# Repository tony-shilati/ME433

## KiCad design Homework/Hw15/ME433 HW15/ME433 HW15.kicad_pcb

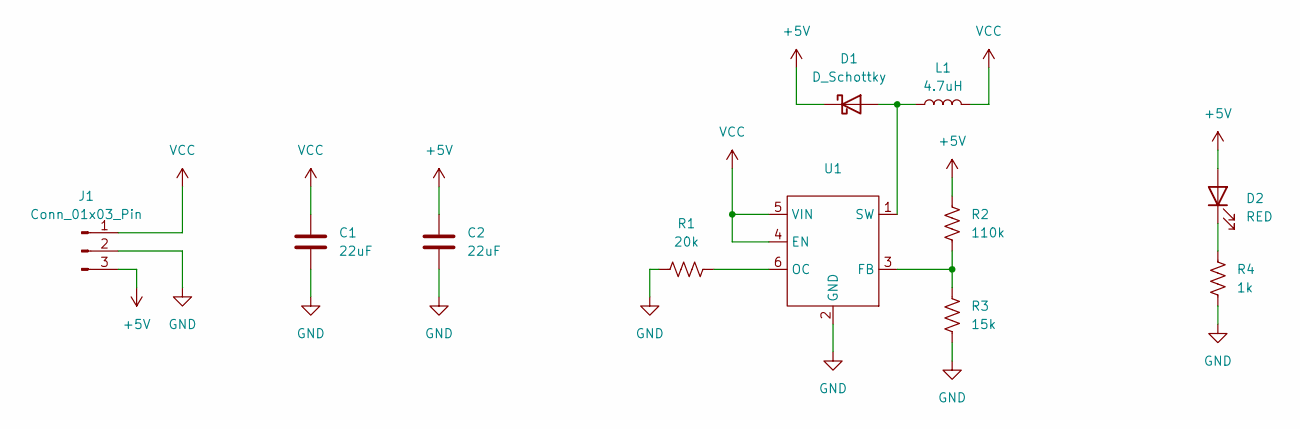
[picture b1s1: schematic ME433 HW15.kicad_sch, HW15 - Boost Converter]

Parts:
C1, C2: 22uF; C_0805_2012Metric
D1: D_Schottky; D_SOD-123
D2: RED; LED_0603_1608Metric
J1: Conn_01x03_Pin; PinHeader_1x03_P2.54mm_Vertical
L1: 4.7uH; L_0603_1608Metric
R1: 20k; R_0603_1608Metric
R2: 110k; R_0402_1005Metric
R3: 15k; R_0402_1005Metric
R4: 1k; R_0603_1608Metric
U1: TSOT-23-6_HandSoldering

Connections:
+5V: C2.1, D1.1 (K), D2.2 (A), J1.3, R2.1
GND: C1.2, C2.2, J1.2, R1.1, R3.2, R4.2, U1.2 (GND)
unnamed: D1.2 (A), L1.1, U1.1 (SW)
unnamed: D2.1 (K), R4.1
unnamed: R2.2, R3.1, U1.3 (FB)
unnamed: R1.2, U1.6 (OC)
VCC: C1.1, J1.1, L1.2, U1.4 (EN), U1.5 (VIN)

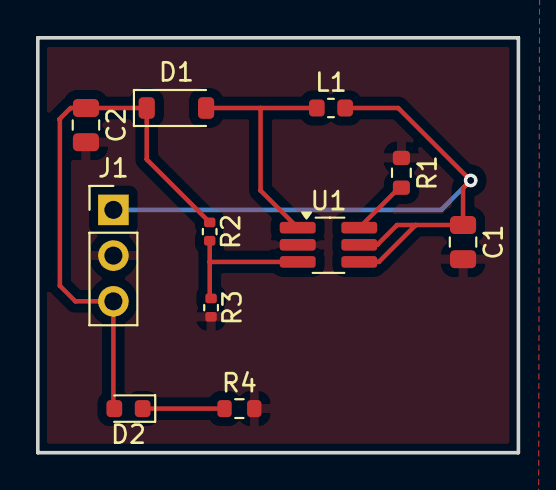
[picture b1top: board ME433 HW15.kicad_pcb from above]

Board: 2 copper layers, 26.7 x 23.0 mm, 11 parts (0 on the bottom side), 7 nets.

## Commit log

2025-04-08 Added hello_gpio_irq and hello_usb
2025-04-08 Removed .DS_Store
2025-04-08 Everything working in Homework 2
2025-04-09 Added the sample code from homework3 on github and ran it
2025-04-09 Most of homework 3 complete.
2025-04-09 Added a picture of the Pico pinout
2025-04-09 I think the Homework 3 code completely works. Still need to check it all
2025-04-12 renamed homework folders and added Hw4 pico project
2025-04-12 Added spi functionality and checked it on the nlab
2025-04-12 Seeing a saw wave on the nlab
2025-04-12 Saw wave is correct amplitude
2025-04-12 Generates a 2Hz triangle wave
2025-04-12 Generates a 1 Hz triangle wave
2025-04-12 Hw4 generates a 2Hz sin wave
2025-04-17 Added a hw5 folder and copied dome of the SPI code from hw4
2025-04-17 Added Waves image for hw4
2025-04-17 Added more spi code
2025-04-18 Wrote a foor loop in the initiation phse, which writes the waveform to the RAM
2025-04-19 Progress. Writing something to the RAM
2025-04-19 Its working git add --all
2025-04-19 added a photo of the waveform and the math
2025-04-21 Added a hearbeat LED
2025-04-21 Pico turns on the LED on startup using the external gpio
2025-04-21 Button and LED work on the external gpio
2025-04-21 Switched the heartbeat LED to be the builtin green led
2025-04-21 Added the vide and rope link
2025-04-23 Added a 1Hz hearbeat LED and downloaded sample code for display
2025-04-23 Made a fun program that sweeps a line back and forth across the display
2025-04-24 Added the font header file
2025-04-24 LED displays each ASCII character on at a time
2025-04-24 Created a function which prints a string on the LED display: git push
2025-04-24 String fills the whole screen
2025-04-24 Added sumitted documents
2025-04-29 Adressable lights are working with the sample code
2025-04-30 Got my Hw8 code working with the ws2812 library. It sets the lights to red green blue and white
2025-04-30 All code works
2025-04-30 Updated timing
2025-05-04 Video demos for hw8
2025-05-04 hello_mulitcore worked. Modifying the code for homework 9
2025-05-04 Using multicore functionality but getting a core1 error
2025-05-04 Finished HW9
2025-05-15 Working fft code
2025-05-15 Removed large files from repo
2025-05-15 Making IIR Filter
2025-05-15 Removed large files
2025-05-15 Added MAF code
2025-05-15 Cleaned up repo
2025-05-15 Finished problem 6
2025-05-15 Finished homework 10
2025-05-17 Mouse moves in a circle on the screen
2025-05-17 Added different modes and can switch by pressing both up and right button. regular mode did not work
2025-05-17 Regular mode works
2025-05-17 Homework 11 complete
2025-05-17 Created Hw13
2025-05-17 Code reads and prints the IMU data
2025-05-27 Added code that creates arrow on the oled display. Need to flip the signs
2025-05-27 Renamed file to help organization
2025-05-27 Hw13 complete
2025-05-27 added photos of robot designs
2025-05-28 Added part datasheets and a screnshot of my schematic. Board Layout to follow
2025-05-29 Hw #15 completed
2025-06-01 pwm is working
2025-06-01 Things are working, but needs some tweaking
2025-06-01 Hw #16 is complete
2025-06-05 Started working towards line following
2025-06-05 Follows the path completely
2025-06-05 Switching to quadratic control funtion
2025-06-05 Final push for ME433

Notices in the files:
Homework/Hw15/ME433 HW15/ME433 HW15.kicad_sch:
creativecommons.org/licenses/by/4.0
License CC BY 4.0
